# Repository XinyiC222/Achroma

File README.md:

# Achroma WORK IN PROGRESS

Achroma is a wireless reversible split keyboard with 36 keys that is powered by ZMK. It uses a nine!nano v2 replica from aliexpress. There are two versions of Achroma, the Choc/Choc_v2 compatible one, and the MX compatible one! This is still a work in progress. Theres only a case for the MX version. But there are two different pcb designs based on which one you want to use. Here is the ZMK source files: https://github.com/XinyiC222/zmk-achroma-config I made this after seeing countless split keyboard builds that people where making online and I wanted to join in on the fun! To use it you just have to turn on the on/off button that is connected to the battery. The pcb is designed in kicad and the case is modeled in Fusion360.

 (MX version)
<h1>Keymap</h1>

<h1>Resources</h1>
<h3>Footprints and References:</h3>

https://github.com/piit79/42keebs-kicad

https://flatfootfox.com/ergogen-part6-reversible-split/

https://github.com/kata0510/Lily58 (this has a great footprint library!)

https://github.com/aroum/PNCATEHO (reversible Choc footprints that fits both versions!)

<h3>Tools</h3>

https://www.keyboard-layout-editor.com/

https://nickcoutsos.github.io/keymap-editor/

https://github.com/adamws/kicad-kbplacer

Fusion360

Kicad

<h1>Mini Guide/ My Process (Work in progress)</h1>

Before starting, you should have already made some kind of electronic project prior to this. It would come off easier if you've designed a pcb before. Reading guides you find online can be super helpful. there are many resources that I didn't link but anything online is helpful. 

1. I first researched and wrote down what I wanted this project to look like at the end. Do I want it to be low profile or MX? Do I want this to be reversible? How much money do I want to spend on this? Do I want to make a custom layout, or do I want to use an existing one? Wireless? etc.
2. I ended up choosing to making my own layout and use ZMK for wireless. So I went ahead and looked for reversible footprints to use. I also wanted to use a battery for it. I then went into keyboard layout editor and made my desired layout.( I only made the left side first)
3. Then I created the schematics in kicad. It included a jst pin, a reversible nice!nano, choc/mx switches, LED, slide switch, and a reset button.
4. then using the .json file from the layout I made in keyboard layout editor and the kbplacer, I organized the keys for the left split.
5. spent a lot of time between editing the schematics, the pcb, and testing new footprint libraries. After a ton of trial and error I made the general layout I wanted.  

6. Exported the gerber files and imported them into jlc pcb.
7. I then added 3d models to each of the footprints and import it into fusion to make the case(MX only) 

8. I looked for components in aliexpress
9. Then I started reading through how to set up ZMK and made the firmware using github actions.
10. After you assemble the pcb and have printed the case out, use a M2 heat insert on all the holes in the case(5 total). Then place the pcb on top and use a M2 screw to tighten it in place.
11. Once you've build the physical item, flash the firmware into the devices. You can learn more about it in the ZMK docs. If you'll like to use the firmware provided, please head to the Firmware folder to download what i have for both the left and the right side.

<h1>Schematic</h1>

<PCB>

<h1>BOM</h1>

Here's the BOM! The Quantity listed below are the amount you need. The links included come in bulks and vary depending on how much you are buyinh. All listed items are required for the build.

| Item | Purpose | Price | Quantity | Source |
| :--- | :--- | :--- | :--- | :--- |
| Nice!Nano V2.0 | Micro controller | $1.95 | 1 | [Aliexpress](https://www.aliexpress.com/item/3256812809465916.html?spm=a2g0o.cart.0.0.564238daJS0mQo&mp=1&pdp_npi=6%40dis%21USD%21USD%2010.84%21USD%203.25%21%21USD%203.25%21%21%21%402101dedf17882176157074667e0e98%2112000059988282797%21ct%21US%217294405090%21%211%210%21) |
| Nice!Nano V2.0 | Micro controller | $2.81 | 1 | [Aliexpress](https://www.aliexpress.com/item/3256807196955871.html?spm=a2g0o.cart.0.0.564238daJS0mQo&mp=1&pdp_npi=6%40dis%21USD%21USD%202.81%21USD%202.64%21%21USD%202.64%21%21%21%402101dedf17882176246834968e0e98%2112000047100969961%21ct%21US%217294405090%21%211%210%21) |
| M2 6mm screws | securing the pcb | $1.37 | x10 | [Aliexpress](https://www.aliexpress.com/item/3256807033160325.html?spm=a2g0o.cart.0.0.564238daJS0mQo&mp=1&pdp_npi=6%40dis%21USD%21USD%201.37%21USD%201.37%21%21USD%201.37%21%21%21%402101dedf17882176157074667e0e98%2112000039933522857%21ct%21US%217294405090%21%211%210%21) |
| M2xL3xOD3.2 heat inserts | for the screws | $0.99 | x10 | [Aliexpress](https://www.aliexpress.com/item/3256806651793931.html?spm=a2g0o.cart.0.0.564238daJS0mQo&mp=1&pdp_npi=6%40dis%21USD%21USD%203.08%21USD%200.99%21%21USD%200.99%21%21%21%402101dedf17882176157074667e0e98%2112000038467725083%21ct%21US%217294405090%21%211%210%21) |
| Gateron Milky Switches | switches | $6.91 | x36 | [Aliexpress](https://www.aliexpress.com/item/3256803874880557.html?spm=a2g0o.cart.0.0.564238daJS0mQo&mp=1&pdp_npi=6%40dis%21USD%21USD%207.35%21USD%206.91%21%21USD%206.91%21%21%21%402101dedf17882176157074667e0e98%2112000027903926419%21ct%21US%217294405090%21%211%210%21) |
| SK6812 MINI-E RGB | RGB | $3.61 | x36 | [Aliexpress](https://www.aliexpress.com/item/3256807677321116.html?spm=a2g0o.cart.0.0.564238daJS0mQo&mp=1&pdp_npi=6%40dis%21USD%21USD%203.61%21USD%203.61%21%21USD%203.61%21%21%21%402101dedf17882176246834968e0e98%2112000042594617264%21ct%21US%217294405090%21%211%210%21) |
| Hotswap Sockets | sockets for switches | $1.33 | x36 | [Aliexpress](https://www.aliexpress.com/item/3256807045726008.html?spm=a2g0o.cart.0.0.564238daJS0mQo&mp=1&pdp_npi=6%40dis%21USD%21USD%202.66%21USD%201.33%21%21USD%201.33%21%21%21%402101dedf17882176157074667e0e98%2112000039893759771%21ct%21US%217294405090%21%211%210%21) |
| Horizontal Microswitch | reset button | $2.04 | x2 | [Aliexpress](https://www.aliexpress.com/item/3256806318779497.html?spm=a2g0o.cart.0.0.564238daJS0mQo&mp=1&pdp_npi=6%40dis%21USD%21USD%202.04%21USD%202.04%21%21USD%202.04%21%21%21%402101dedf17882176246834968e0e98%2112000037444053760%21ct%21US%217294405090%21%211%210%21) |
| PH 2.0 Horizontal Header Socket | for the battery | $1.80 | x2 | [Aliexpress](https://www.aliexpress.com/item/3256808824951678.html?spm=a2g0o.cart.0.0.564238daJS0mQo&mp=1&pdp_npi=6%40dis%21USD%21USD%201.80%21USD%201.80%21%21USD%201.80%21%21%21%402101dedf17882176293735149e0e98%2112000047583383492%21ct%21US%217294405090%21%211%210%21&pdp_ext_f=%7B%22cart2PdpParams%22%3A%7B%22pdpBusinessMode%22%3A%22retail%22%7D%7D) |
| SS12D00G3 Toggle Switch | battery on/off | $0.92 | x2 | [Aliexpress](https://www.aliexpress.com/item/3256808561935510.html?spm=a2g0o.cart.0.0.564238daJS0mQo&mp=1&pdp_npi=6%40dis%21USD%21USD%200.92%21USD%200.92%21%21USD%200.92%21%21%21%402101dedf17882176319215275e0e98%2112000046504078875%21ct%21US%217294405090%21%211%210%21) |
| IN4148 SOD-123 | diodes | $2.08 | x36 | [Aliexpress](https://www.aliexpress.com/item/2255800498728983.html?spm=a2g0o.cart.0.0.564238daJS0mQo&mp=1&pdp_npi=6%40dis%21USD%21USD%202.08%21USD%202.08%21%21USD%202.08%21%21%21%402101dedf17882176365865480e0e98%2112000037997014577%21ct%21US%217294405090%21%211%210%21) |
| 401030 3.7V 110mAh Polymer Lithium Battery | Battery | $9.72 | x2 | [Aliexpress](https://www.aliexpress.us/item/3256811360999976.html?mp=1&pdp_npi=6@dis!USD!USD+11.30!USD+9.72!!USD+9.72!!!@210328df17882265747402256e0fd1!12000055885084344!ct!US!7294405090!!1!0!&gatewayAdapt=glo2usa) |
| Case | cover | | x2 | 3d Printed |
| PCB | connect everything together | $9.60 | x2 | JLCPCB |
| **Aliexpress Subtotal** | | **$36.66** | | |
| **JLC Subtotal** | | **$9.60** | | |
| **shipping+tax** | | **+$12.24** | | |
| **Total:** | | **$58.50** | | |

## Credits
<div align="center">

</div>

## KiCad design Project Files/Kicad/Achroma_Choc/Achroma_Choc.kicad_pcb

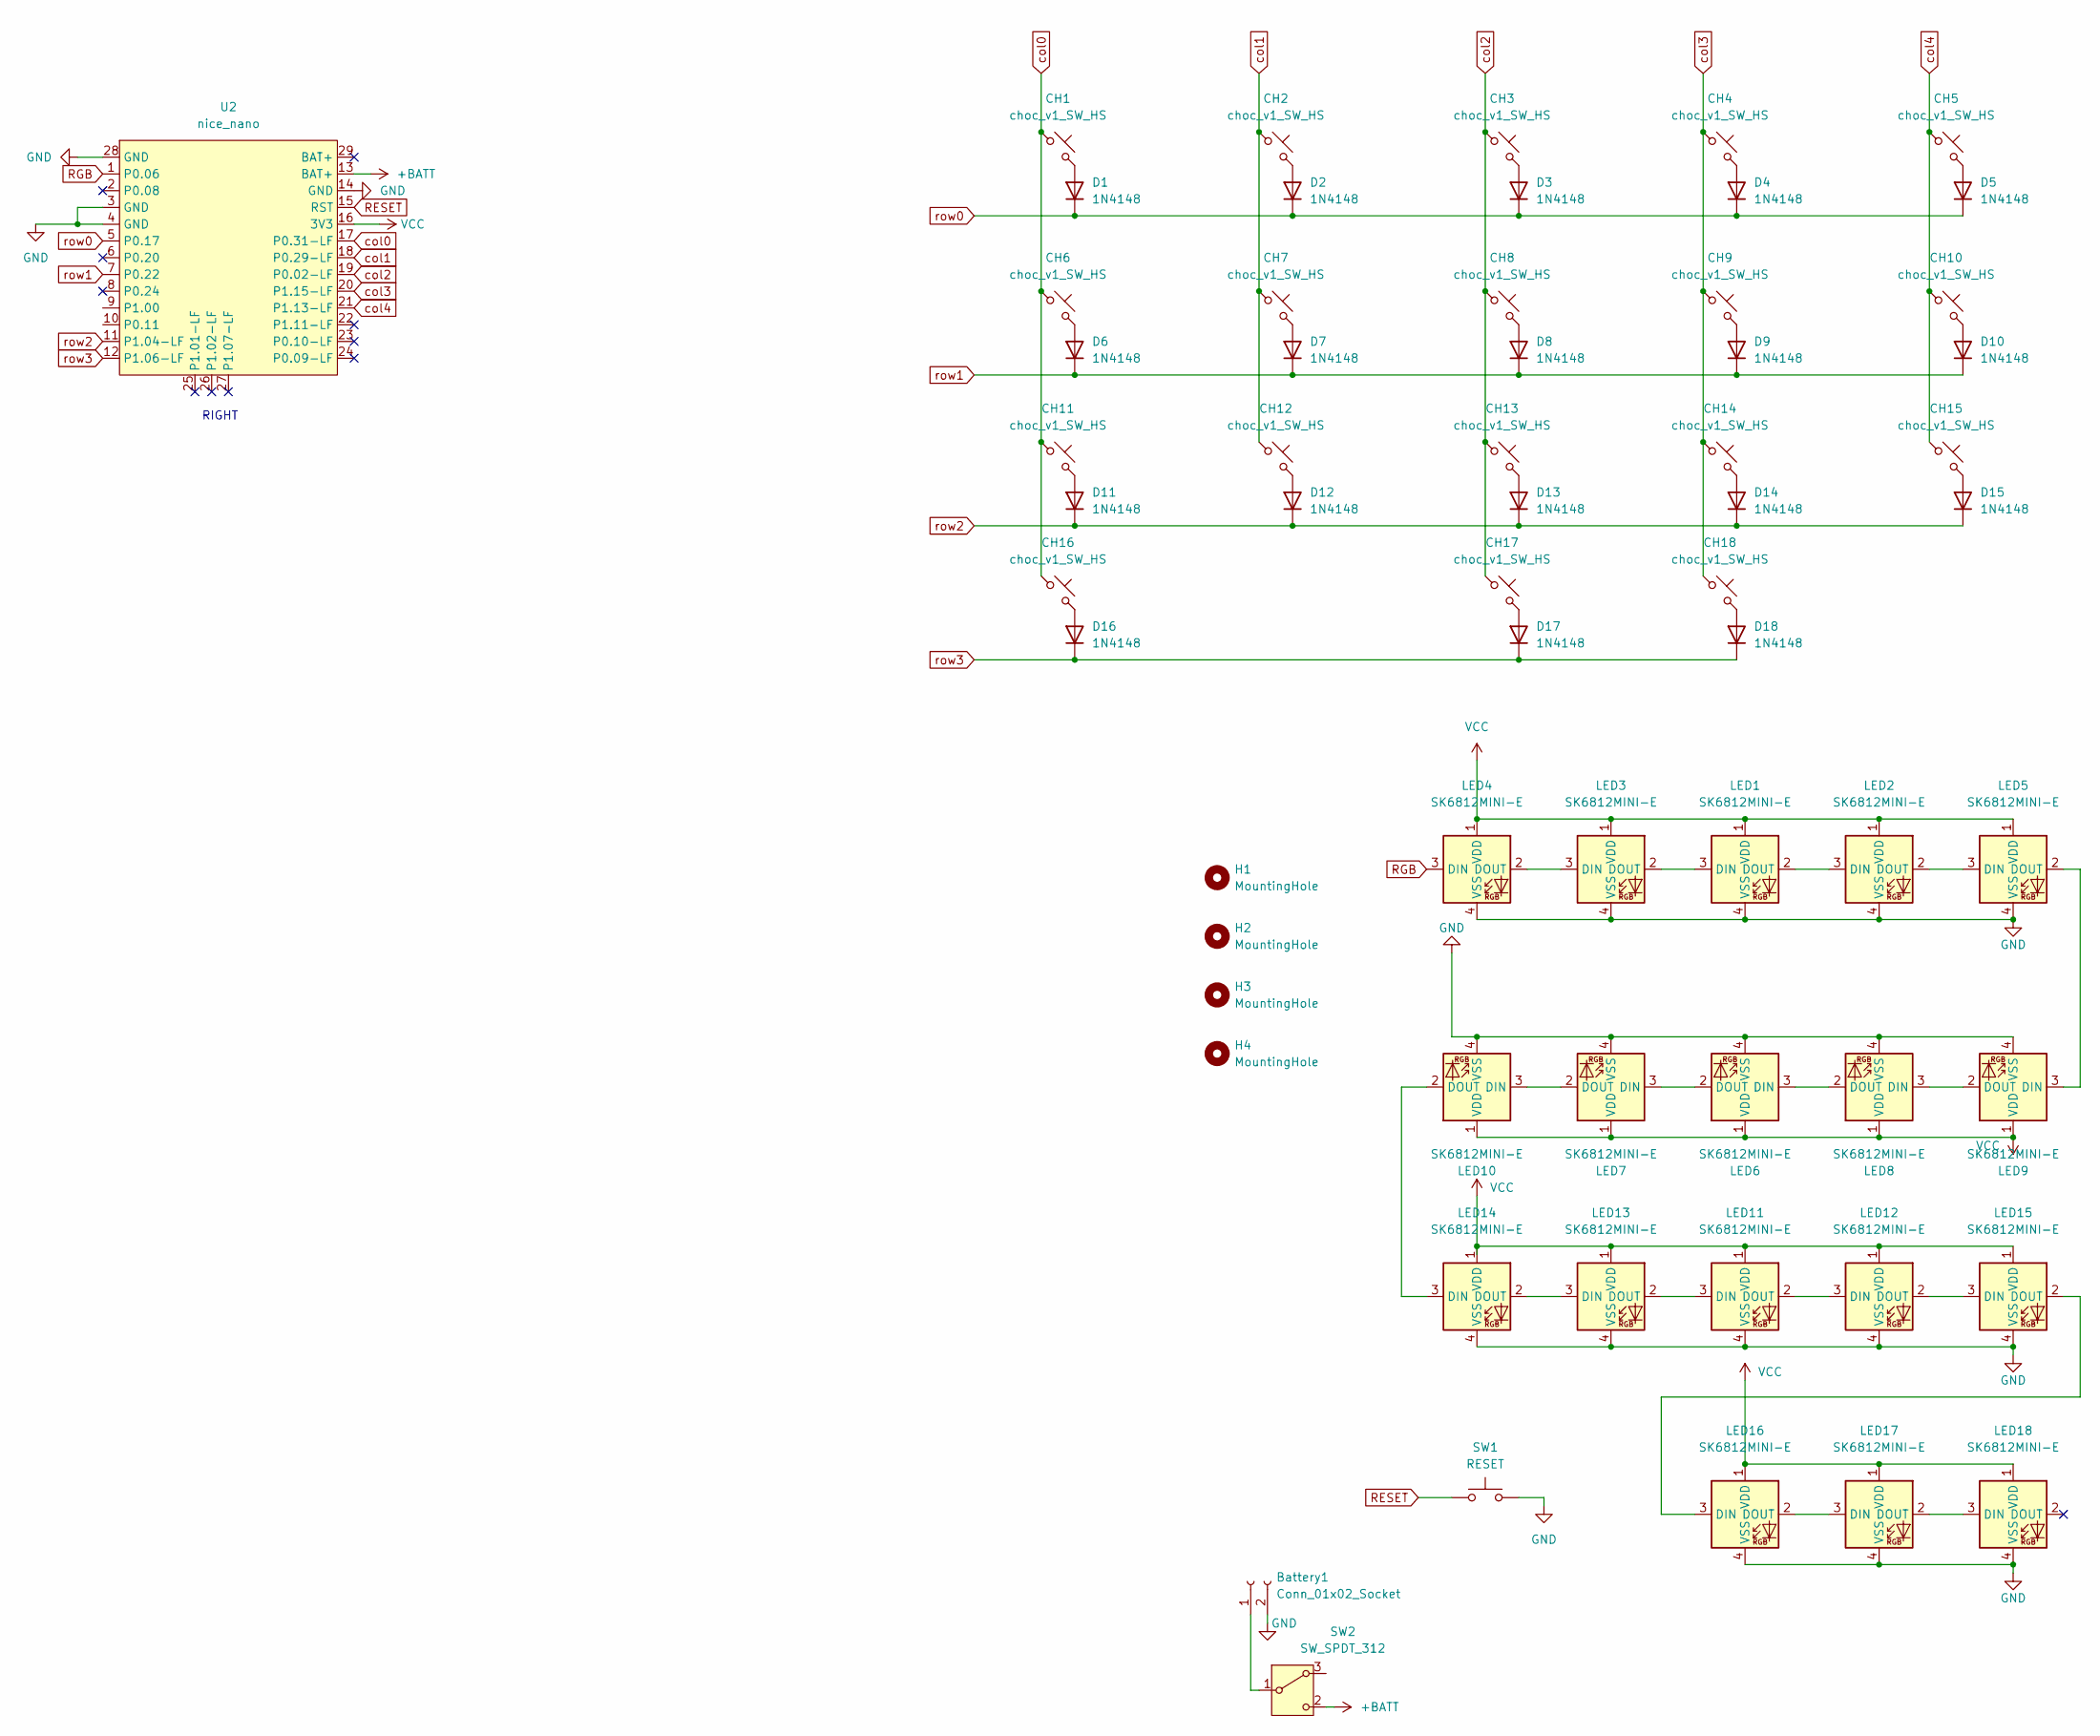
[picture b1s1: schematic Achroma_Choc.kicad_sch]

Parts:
Battery1: Conn_01x02_Socket; JST_PH_S2B-PH-SM4-TB_1x02-1MP_P2.00mm_Horizontal
CH1, CH2, CH3, CH4, CH5, CH6, CH7, CH8, CH9, CH10, CH11, CH12, CH13, CH14, CH15, CH16, CH17, CH18: choc_v1_SW_HS; Kailh_socket_PG1350_reversible
D1, D2, D3, D4, D5, D6, D7, D8, D9, D10, D11, D12, D13, D14, D15, D16, D17, D18: 1N4148; D_SOD-123 Reversible
H1, H2, H3, H4: MountingHole; MountingHole_2.1mm
LED1, LED2, LED3, LED4, LED5, LED6, LED7, LED8, LED9, LED10, LED11, LED12, LED13, LED14, LED15, LED16, LED17, LED18: SK6812MINI-E; LED_6028R_Reversible
SW1: RESET; TACT_SWITCH_TVBP06
SW2: SW_SPDT_312; SS12D00
U2: nice_nano; nice_nano_AH_Reversible

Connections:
+BATT: SW2.2 (C), U2.13 (BAT+)
GND: Battery1.2, LED1.4 (VSS), LED2.4 (VSS), LED3.4 (VSS), LED4.4 (VSS), LED5.4 (VSS), LED6.4 (VSS), LED7.4 (VSS), LED8.4 (VSS), LED9.4 (VSS), LED10.4 (VSS), LED11.4 (VSS), LED12.4 (VSS), LED13.4 (VSS), LED14.4 (VSS), LED15.4 (VSS), LED16.4 (VSS), LED17.4 (VSS), LED18.4 (VSS), SW1.2, U2.3 (GND), U2.4 (GND), U2.14 (GND), U2.28 (GND)
unnamed: Battery1.1, SW2.1 (B)
unnamed: CH1.2, D1.2 (A)
unnamed: CH2.2, D2.2 (A)
unnamed: CH3.2, D3.2 (A)
unnamed: CH4.2, D4.2 (A)
unnamed: CH5.2, D5.2 (A)
unnamed: CH6.2, D6.2 (A)
unnamed: CH7.2, D7.2 (A)
unnamed: CH8.2, D8.2 (A)
unnamed: CH9.2, D9.2 (A)
unnamed: CH10.2, D10.2 (A)
unnamed: CH11.2, D11.2 (A)
unnamed: CH12.2, D12.2 (A)
unnamed: CH13.2, D13.2 (A)
unnamed: CH14.2, D14.2 (A)
unnamed: CH15.2, D15.2 (A)
unnamed: CH16.2, D16.2 (A)
unnamed: CH17.2, D17.2 (A)
unnamed: CH18.2, D18.2 (A)
unnamed: LED1.3 (DIN), LED3.2 (DOUT)
unnamed: LED1.2 (DOUT), LED2.3 (DIN)
unnamed: LED2.2 (DOUT), LED5.3 (DIN)
unnamed: LED3.3 (DIN), LED4.2 (DOUT)
unnamed: LED5.2 (DOUT), LED9.3 (DIN)
unnamed: LED6.3 (DIN), LED8.2 (DOUT)
unnamed: LED6.2 (DOUT), LED7.3 (DIN)
unnamed: LED8.3 (DIN), LED9.2 (DOUT)
unnamed: LED7.2 (DOUT), LED10.3 (DIN)
unnamed: LED10.2 (DOUT), LED14.3 (DIN)
unnamed: LED11.3 (DIN), LED13.2 (DOUT)
unnamed: LED11.2 (DOUT), LED12.3 (DIN)
unnamed: LED12.2 (DOUT), LED15.3 (DIN)
unnamed: LED13.3 (DIN), LED14.2 (DOUT)
unnamed: LED15.2 (DOUT), LED16.3 (DIN)
unnamed: LED16.2 (DOUT), LED17.3 (DIN)
unnamed: LED17.2 (DOUT), LED18.3 (DIN)
RESET: SW1.1, U2.15 (RST)
RGB: LED4.3 (DIN), U2.1 (P0.06)
VCC: LED1.1 (VDD), LED2.1 (VDD), LED3.1 (VDD), LED4.1 (VDD), LED5.1 (VDD), LED6.1 (VDD), LED7.1 (VDD), LED8.1 (VDD), LED9.1 (VDD), LED10.1 (VDD), LED11.1 (VDD), LED12.1 (VDD), LED13.1 (VDD), LED14.1 (VDD), LED15.1 (VDD), LED16.1 (VDD), LED17.1 (VDD), LED18.1 (VDD), U2.16 (3V3)
col0: CH1.1, CH6.1, CH11.1, CH16.1, U2.17 (P0.31-LF)
col1: CH2.1, CH7.1, CH12.1, U2.18 (P0.29-LF)
col2: CH3.1, CH8.1, CH13.1, CH17.1, U2.19 (P0.02-LF)
col3: CH4.1, CH9.1, CH14.1, CH18.1, U2.20 (P1.15-LF)
col4: CH5.1, CH10.1, CH15.1, U2.21 (P1.13-LF)
row0: D1.1 (K), D2.1 (K), D3.1 (K), D4.1 (K), D5.1 (K), U2.5 (P0.17)
row1: D6.1 (K), D7.1 (K), D8.1 (K), D9.1 (K), D10.1 (K), U2.7 (P0.22)
row2: D11.1 (K), D12.1 (K), D13.1 (K), D14.1 (K), D15.1 (K), U2.11 (P1.04-LF)
row3: D16.1 (K), D17.1 (K), D18.1 (K), U2.12 (P1.06-LF)

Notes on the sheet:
RIGHT

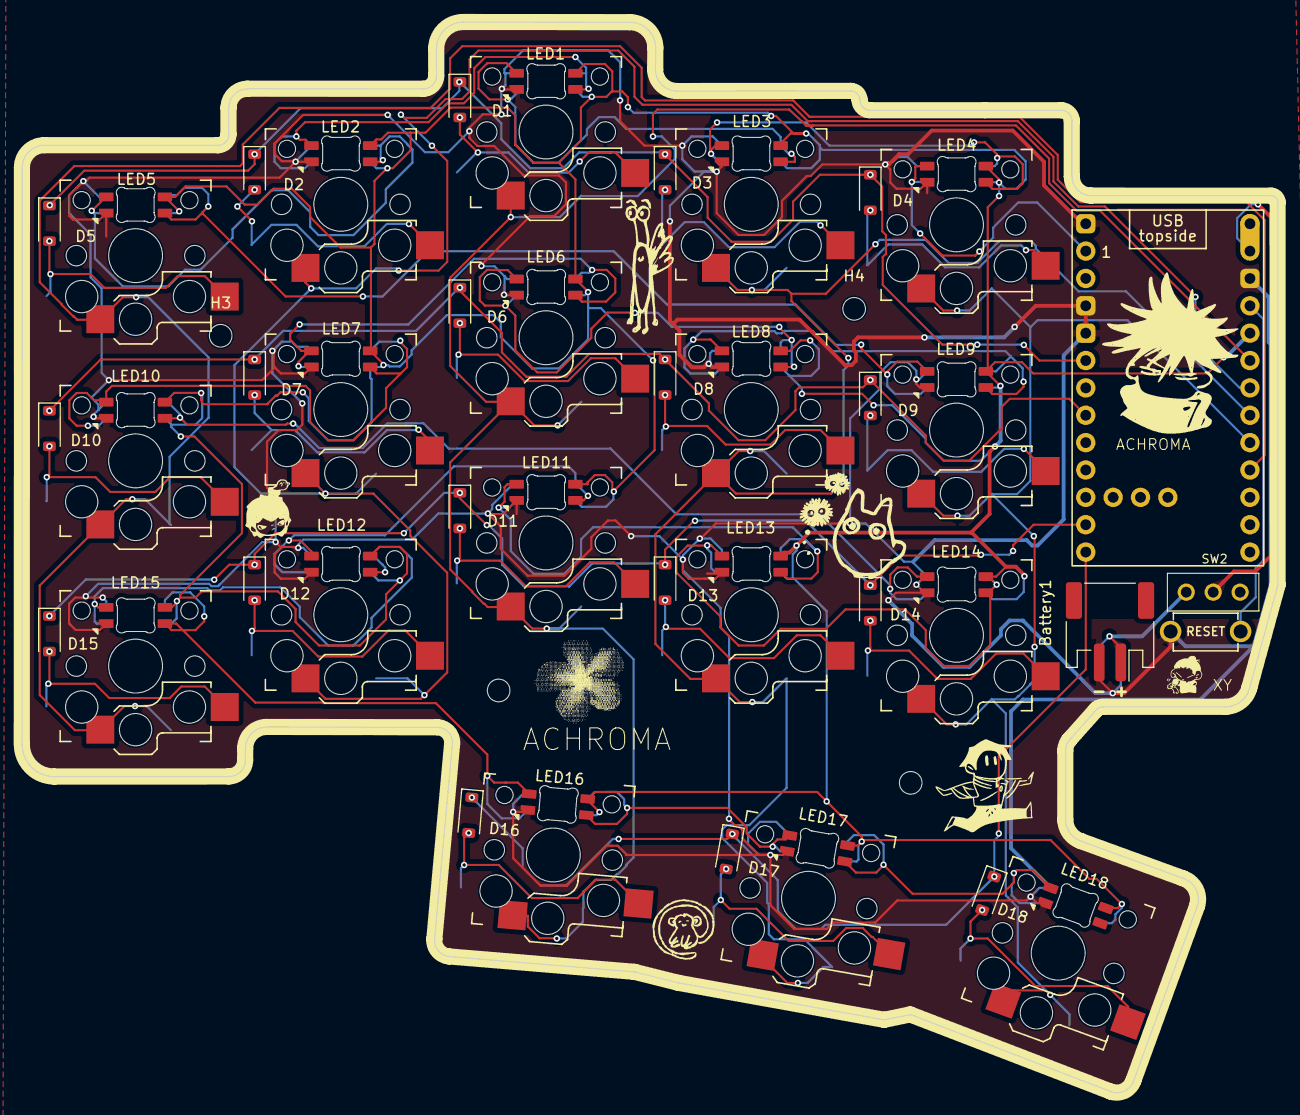
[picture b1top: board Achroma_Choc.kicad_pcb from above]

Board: 2 copper layers, 116.6 x 99.4 mm, 62 parts (0 on the bottom side), 50 nets.
